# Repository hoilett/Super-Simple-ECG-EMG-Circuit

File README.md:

DEPRECATED
# Super-Simple-ECG-EMG-Circuit

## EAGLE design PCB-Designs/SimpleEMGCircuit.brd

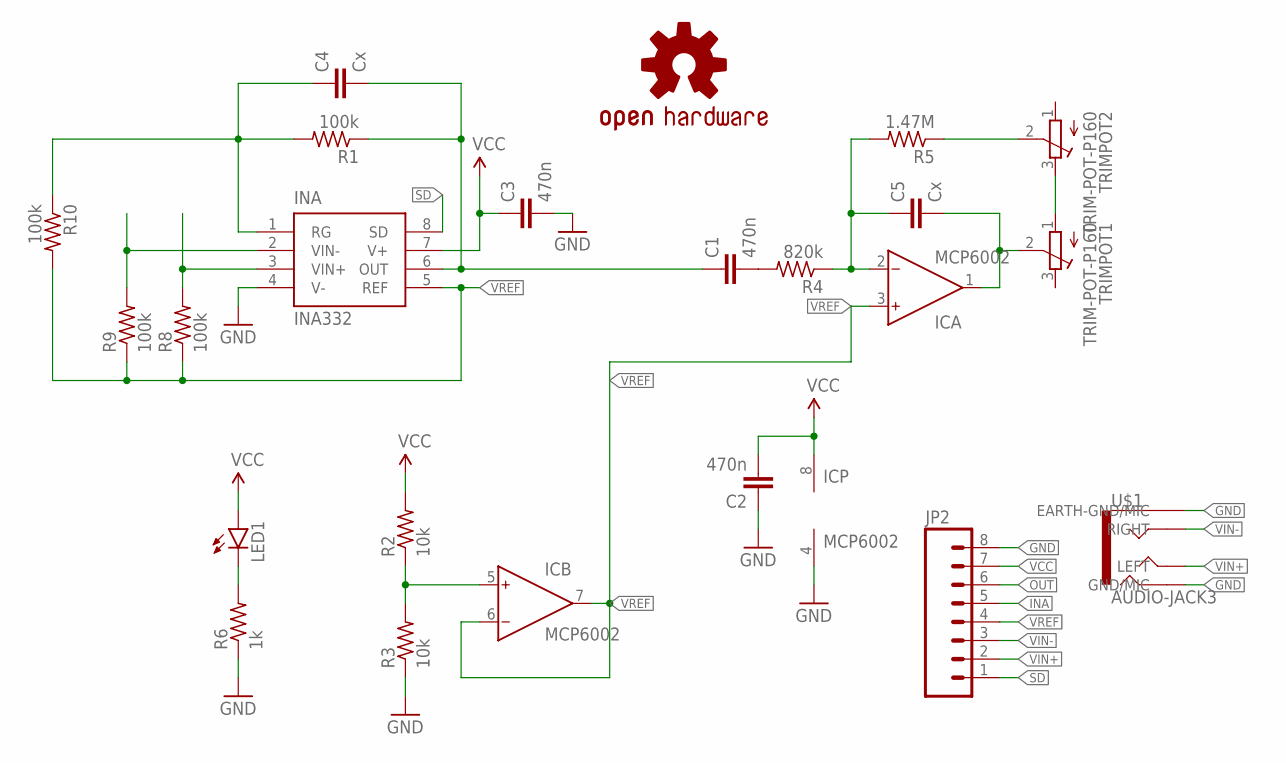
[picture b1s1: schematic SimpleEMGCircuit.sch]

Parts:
C1, C2, C3: 470n; C0402
C4, C5: Cx; C0402
IC: MCP6002; MSOP08
INA: INA332; MSOP08
JP2: M08NO_SILK_FEMALE_PTH; 1X08_NO_SILK
LED1: LED0603; LED-0603
LOGO1: OSHW-LOGOS; OSHW-LOGO-S
R1, R8, R9, R10: 100k; R0402
R2, R3: 10k; R0402
R4: 820k; R0402
R5: 1.47M; R0402
R6: 1k; R0402
TRIMPOT1, TRIMPOT2: TRIM-POT-P160; 16MMROTARYPOT
U$1: AUDIO-JACK3; AUDIO-JACK-TRRS-SMD

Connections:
GND: C2.1, C3.2, IC.4 (V-), INA.4 (V-), JP2.8, R3.1, R6.1, U$1.EARTH (EARTH-GND/MIC), U$1.RING2 (GND/MIC)
INA: C1.1, C4.2, INA.6 (OUT), JP2.5, R1.1
unnamed: C4.1, INA.1 (RG), R1.2, R10.1
unnamed: TRIMPOT1.1 (A), TRIMPOT2.3 (E)
unnamed: IC.5 (IN+), R2.1, R3.2
unnamed: C1.2, R4.2
unnamed: C5.1, IC.2 (IN-), R4.1, R5.2
unnamed: LED1.C, R6.2
unnamed: R5.1, TRIMPOT2.2 (S)
OUT: C5.2, IC.1 (OUT), JP2.6, TRIMPOT1.2 (S)
SD: INA.8 (SD), JP2.1
VCC: C2.2, C3.1, IC.8 (V+), INA.7 (V+), JP2.7, LED1.A, R2.2
VIN+: INA.3 (VIN+), JP2.2, R8.2, U$1.TIP (LEFT)
VIN-: INA.2 (VIN-), JP2.3, R9.2, U$1.RING1 (RIGHT)
VREF: IC.3 (IN+), IC.6 (IN-), IC.7 (OUT), INA.5 (REF), JP2.4, R8.1, R9.1, R10.2

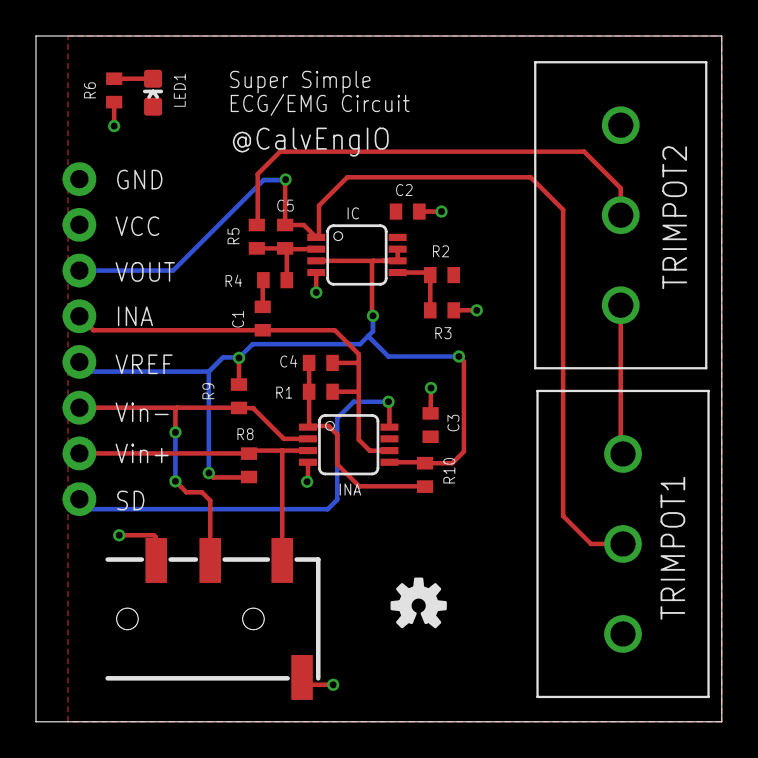
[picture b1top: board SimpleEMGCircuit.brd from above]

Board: 2 copper layers, 38.1 x 38.1 mm, 22 parts (0 on the bottom side), 15 nets.

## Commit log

2016-11-13 Update LICENSE
2016-11-13 Rename LICENSE to LICENSE-hardware
2016-11-13 pcb designs
2016-11-13 removed autosave files

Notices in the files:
PCB-Designs/SimpleEMGCircuit.brd:
Creative Commons License
CC BY-SA-4.0
parts and their libraries:
SparkFun-Connectors: Licensing: Creative Commons ShareAlike 4.0 International - https://creativecommons.org/licenses/by-sa/4.0
